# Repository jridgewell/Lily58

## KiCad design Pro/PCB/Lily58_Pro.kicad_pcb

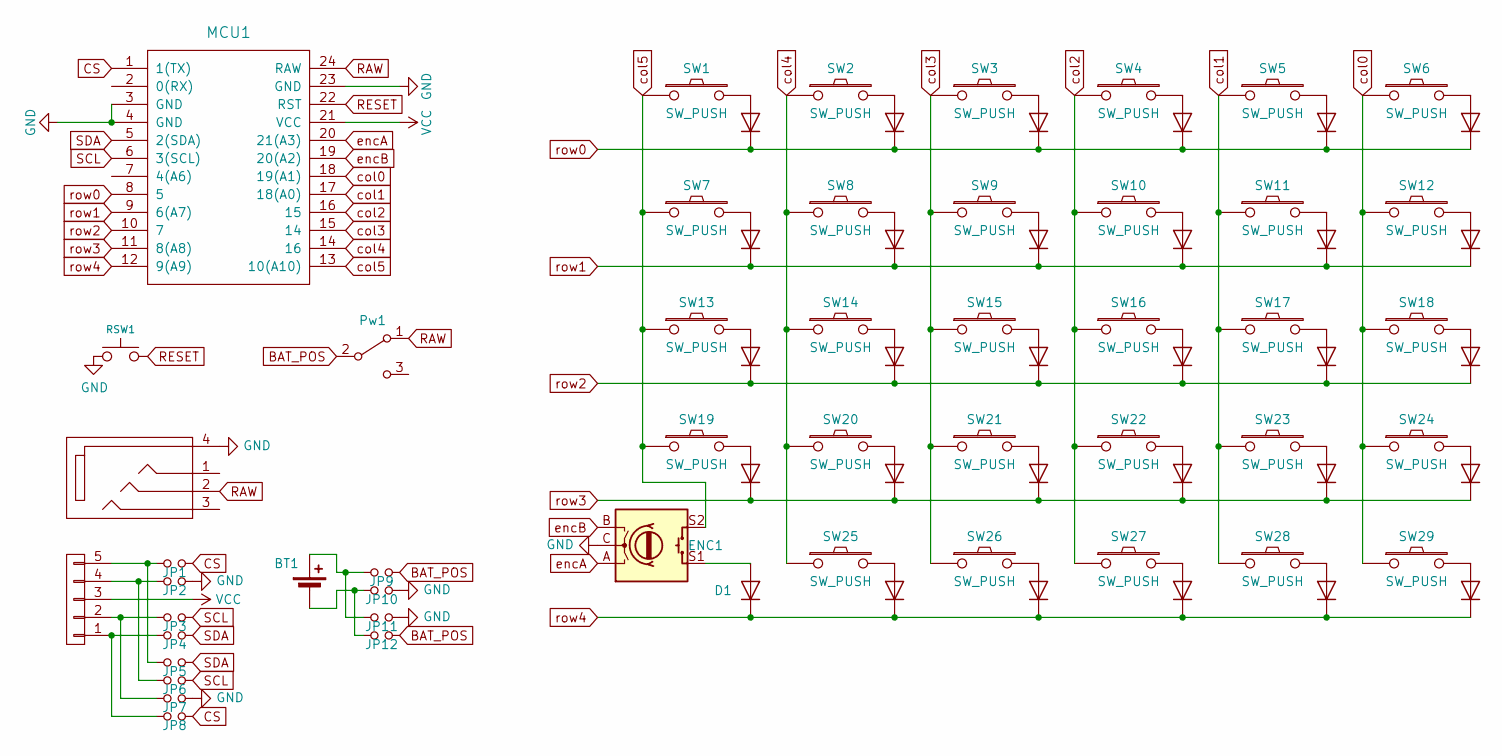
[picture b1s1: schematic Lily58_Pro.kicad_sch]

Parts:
BT1: Battery_Cell; Battery
D1: Lily58:D; Diode_SOD123
ENC1: RotaryEncoder_Switch; RotaryEncoder_EC11
J1: OLED; NiceView_5Pin
J2: TRRS; MJ-4PP-9
JP1, JP2, JP3, JP4, JP5, JP6, JP7, JP8, JP9, JP10, JP11, JP12: Jumper_arrow
MCU1: NiceNano; ProMicro_rev3
Pw1: SW_SPDT; Power_Switch
RSW1: SW_RST; Reset_Button
SW1, SW2, SW3, SW4, SW5, SW6, SW7, SW8, SW9, SW10, SW11, SW12, SW13, SW14, SW15, SW16, SW17, SW18: SW_PUSH; MX_Choc_Hotswap_bottom_diode
SW19, SW20, SW21, SW22, SW23, SW24: SW_PUSH; MX_Choc_Hotswap_left_diode
SW25, SW26: SW_PUSH; MX_Choc_Hotswap_right_diode
SW27, SW28, SW29: SW_PUSH; MX_Choc_Hotswap_top_diode

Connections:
BAT_POS: JP9.2, JP12.2, Pw1.2 (B)
CS: JP1.2, JP8.2, MCU1.1 (1(TX))
GND: ENC1.C, J2.4, JP2.2, JP7.2, JP10.2, JP11.2, MCU1.3 (GND), MCU1.4 (GND), MCU1.23 (GND), RSW1.1
unnamed: BT1.1 (+), JP9.1, JP11.1
unnamed: BT1.2 (-), JP10.1, JP12.1
unnamed: D1.2 (A), ENC1.S1
unnamed: J1.1, JP4.1, JP8.1
unnamed: J1.2, JP3.1, JP7.1
unnamed: J1.4, JP2.1, JP6.1
unnamed: J1.5, JP1.1, JP5.1
RAW: J2.2, MCU1.24 (RAW), Pw1.1 (A)
RESET: MCU1.22 (RST), RSW1.2
SCL: JP3.2, JP6.2, MCU1.6 (3(SCL))
SDA: JP4.2, JP5.2, MCU1.5 (2(SDA))
VCC: J1.3, MCU1.21 (VCC)
col0: MCU1.18 (19(A1)), SW6.1, SW12.1, SW18.1, SW24.1, SW29.1
col1: MCU1.17 (18(A0)), SW5.1, SW11.1, SW17.1, SW23.1, SW28.1
col2: MCU1.16 (15), SW4.1, SW10.1, SW16.1, SW22.1, SW27.1
col3: MCU1.15 (14), SW3.1, SW9.1, SW15.1, SW21.1, SW26.1
col4: MCU1.14 (16), SW2.1, SW8.1, SW14.1, SW20.1, SW25.1
col5: ENC1.S2, MCU1.13 (10(A10)), SW1.1, SW7.1, SW13.1, SW19.1
encA: ENC1.A, MCU1.20 (21(A3))
encB: ENC1.B, MCU1.19 (20(A2))
row0: MCU1.8 (5), SW1.3 (K), SW2.3 (K), SW3.3 (K), SW4.3 (K), SW5.3 (K), SW6.3 (K)
row1: MCU1.9 (6(A7)), SW7.3 (K), SW8.3 (K), SW9.3 (K), SW10.3 (K), SW11.3 (K), SW12.3 (K)
row2: MCU1.10 (7), SW13.3 (K), SW14.3 (K), SW15.3 (K), SW16.3 (K), SW17.3 (K), SW18.3 (K)
row3: MCU1.11 (8(A8)), SW19.3 (K), SW20.3 (K), SW21.3 (K), SW22.3 (K), SW23.3 (K), SW24.3 (K)
row4: D1.1 (K), MCU1.12 (9(A9)), SW25.3 (K), SW26.3 (K), SW27.3 (K), SW28.3 (K), SW29.3 (K)

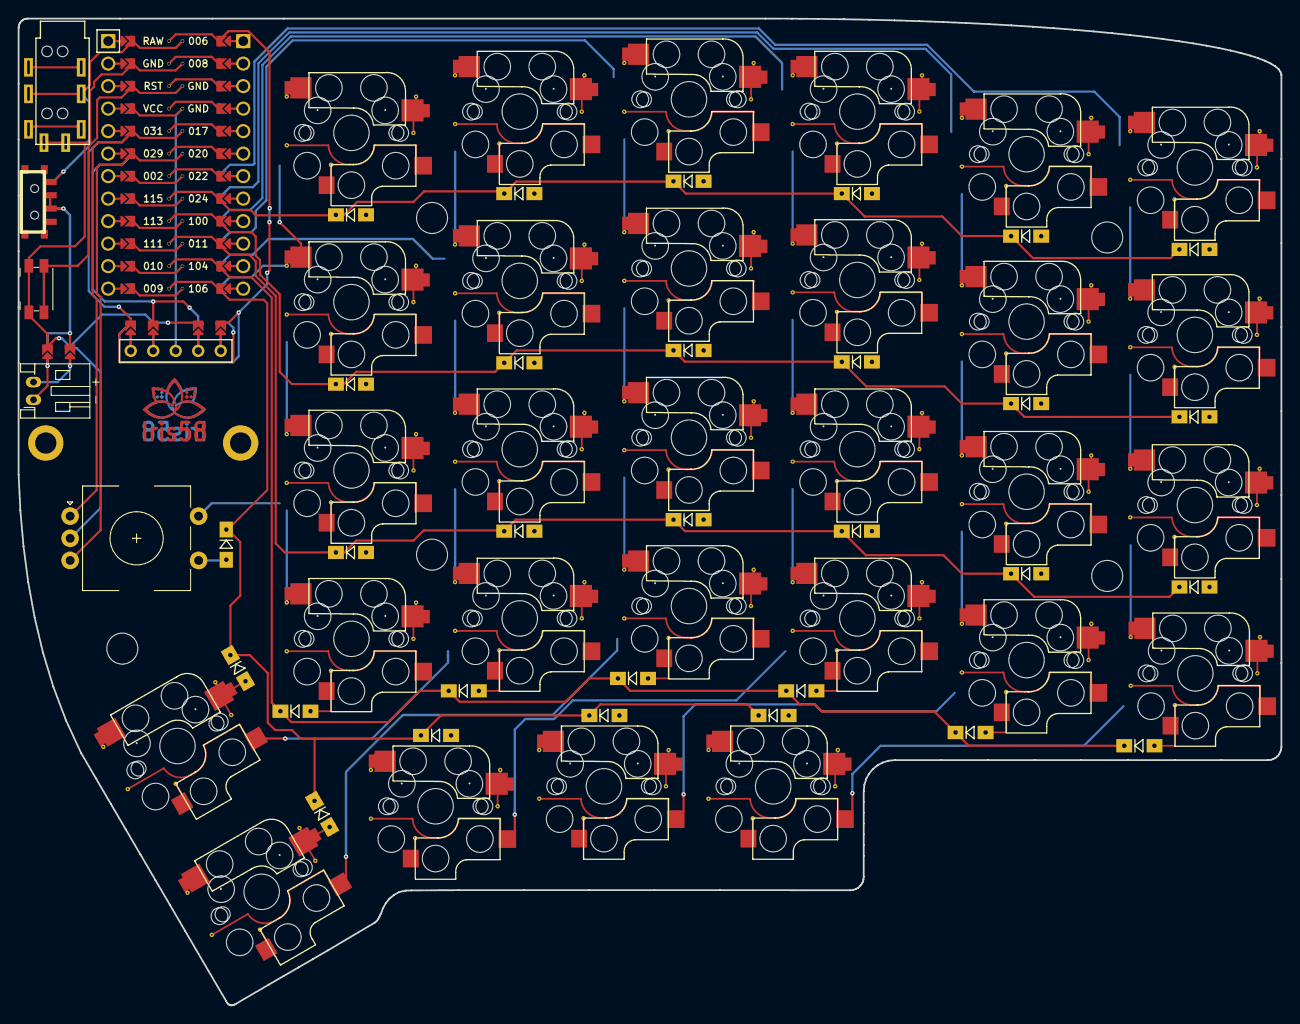
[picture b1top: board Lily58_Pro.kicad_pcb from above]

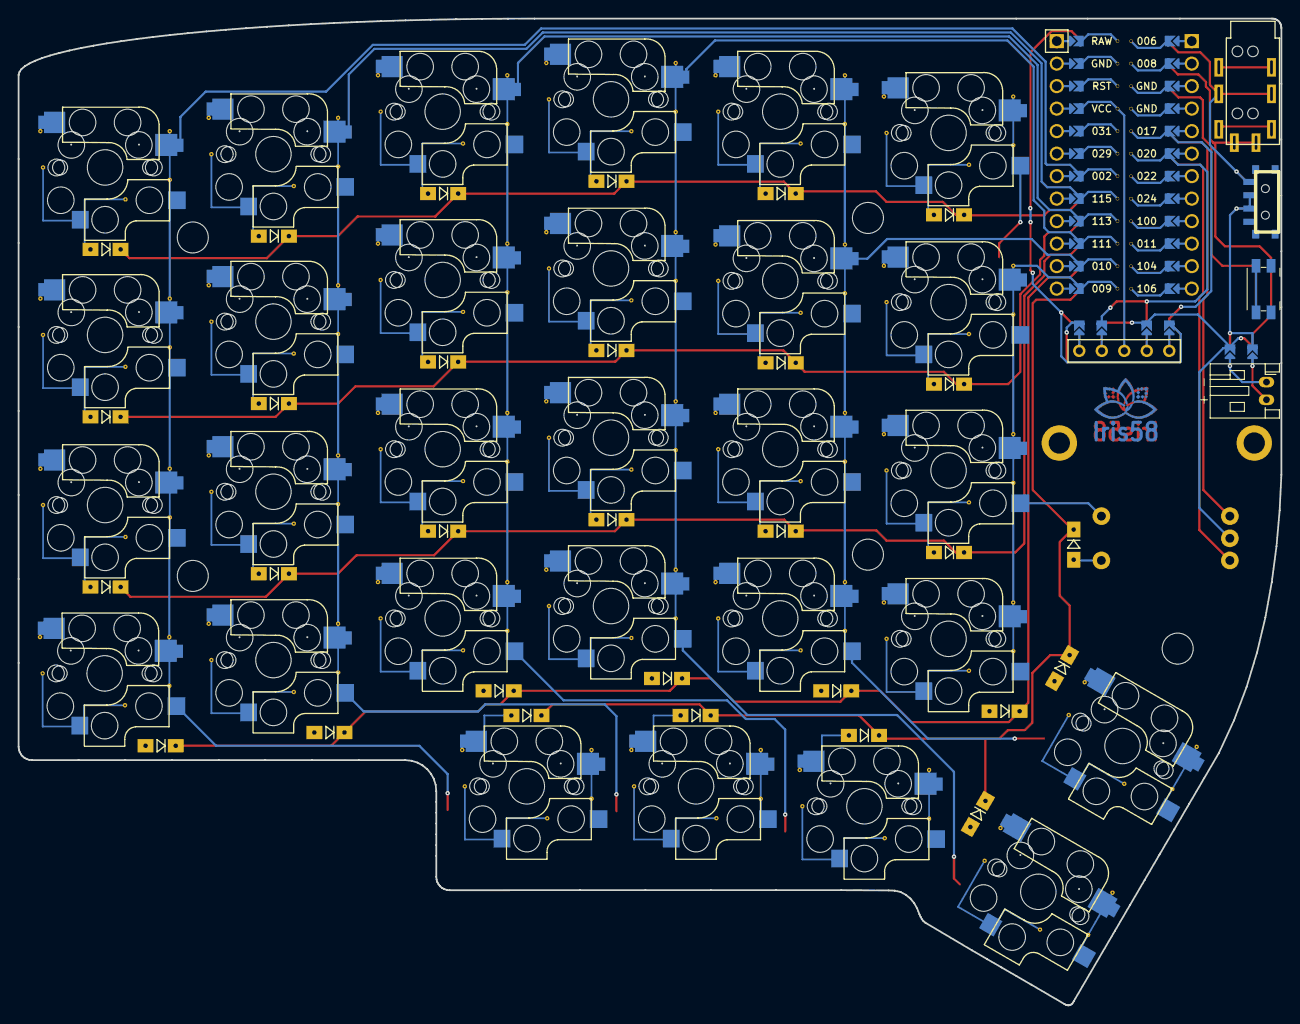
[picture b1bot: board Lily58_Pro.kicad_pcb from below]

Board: 2 copper layers, 142.5 x 111.4 mm, 56 parts (6 on the bottom side), 28 nets.

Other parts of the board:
TH1, TH2: HOLE; M2_HOLE_PCB
TH3, TH4, TH5, TH6, TH7: HOLE; HOLE_M2_Standoff

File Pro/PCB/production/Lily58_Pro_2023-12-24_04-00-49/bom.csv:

Designator,Footprint,Quantity,Value,LCSC Part #
BT1,Battery,1,Battery_Cell,
D1,Diode_SOD123,1,Lily58-cache:D,
ENC1,RotaryEncoder_Alps_EC11E-Switch_Vertical_H20mm,1,RotaryEncoder_Switch,
J1,NiceView_5Pin,1,OLED,
J2,MJ-4PP-9,1,TRRS,
"JP1, JP10, JP11, JP12, JP2, JP3, JP4, JP5, JP6, JP7, JP8, JP9",Jumper_arrow,12,~,
MCU1,ProMicro_rev3,1,NiceNano,
Pw1,Power_Switch,1,SW_SPDT,
RSW1,Reset_Button,1,SW_RST,
"SW1, SW10, SW11, SW12, SW13, SW14, SW15, SW16, SW17, SW18, SW19, SW2, SW20, SW21, SW22, SW23, SW24, SW3, SW4, SW5, SW6, SW7, SW8, SW9",MX_Choc_Hotswap_bottom_diode,24,SW_PUSH,
"SW25, SW26",MX_Choc_Hotswap_right_diode,2,SW_PUSH,
"SW27, SW28, SW29",MX_Choc_Hotswap_top_diode,3,SW_PUSH,
"TH1, TH2",M2_HOLE_PCB,2,HOLE,
"TH3, TH4, TH5, TH6, TH7",HOLE_M2_Standoff,5,HOLE,

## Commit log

2023-12-20 Adjust thumb positions, add battery switch
    Also powers/charges both sides
2023-12-24 Remove old files
2023-12-24 Production run
2023-12-24 Cleanup
2024-01-03 Small fixes
